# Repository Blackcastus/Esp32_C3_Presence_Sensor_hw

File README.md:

# Esp32_C3_Presence_Sensor_hw
## Thông tin
1. Sử dụng nguồn 220VAC
2. Cảm biến hiện diện HLK-LD2410
3. MCU: ESP32-C3
4. Giao tiếp: USB, UART
5. Extra: DS18820, quang trở
6. Màn hình oled 128
7. Output relay 220VAC
8. Mạch thu RF 315Mhz
9. Màn hình tft ili9341 2.2 inch 18pin

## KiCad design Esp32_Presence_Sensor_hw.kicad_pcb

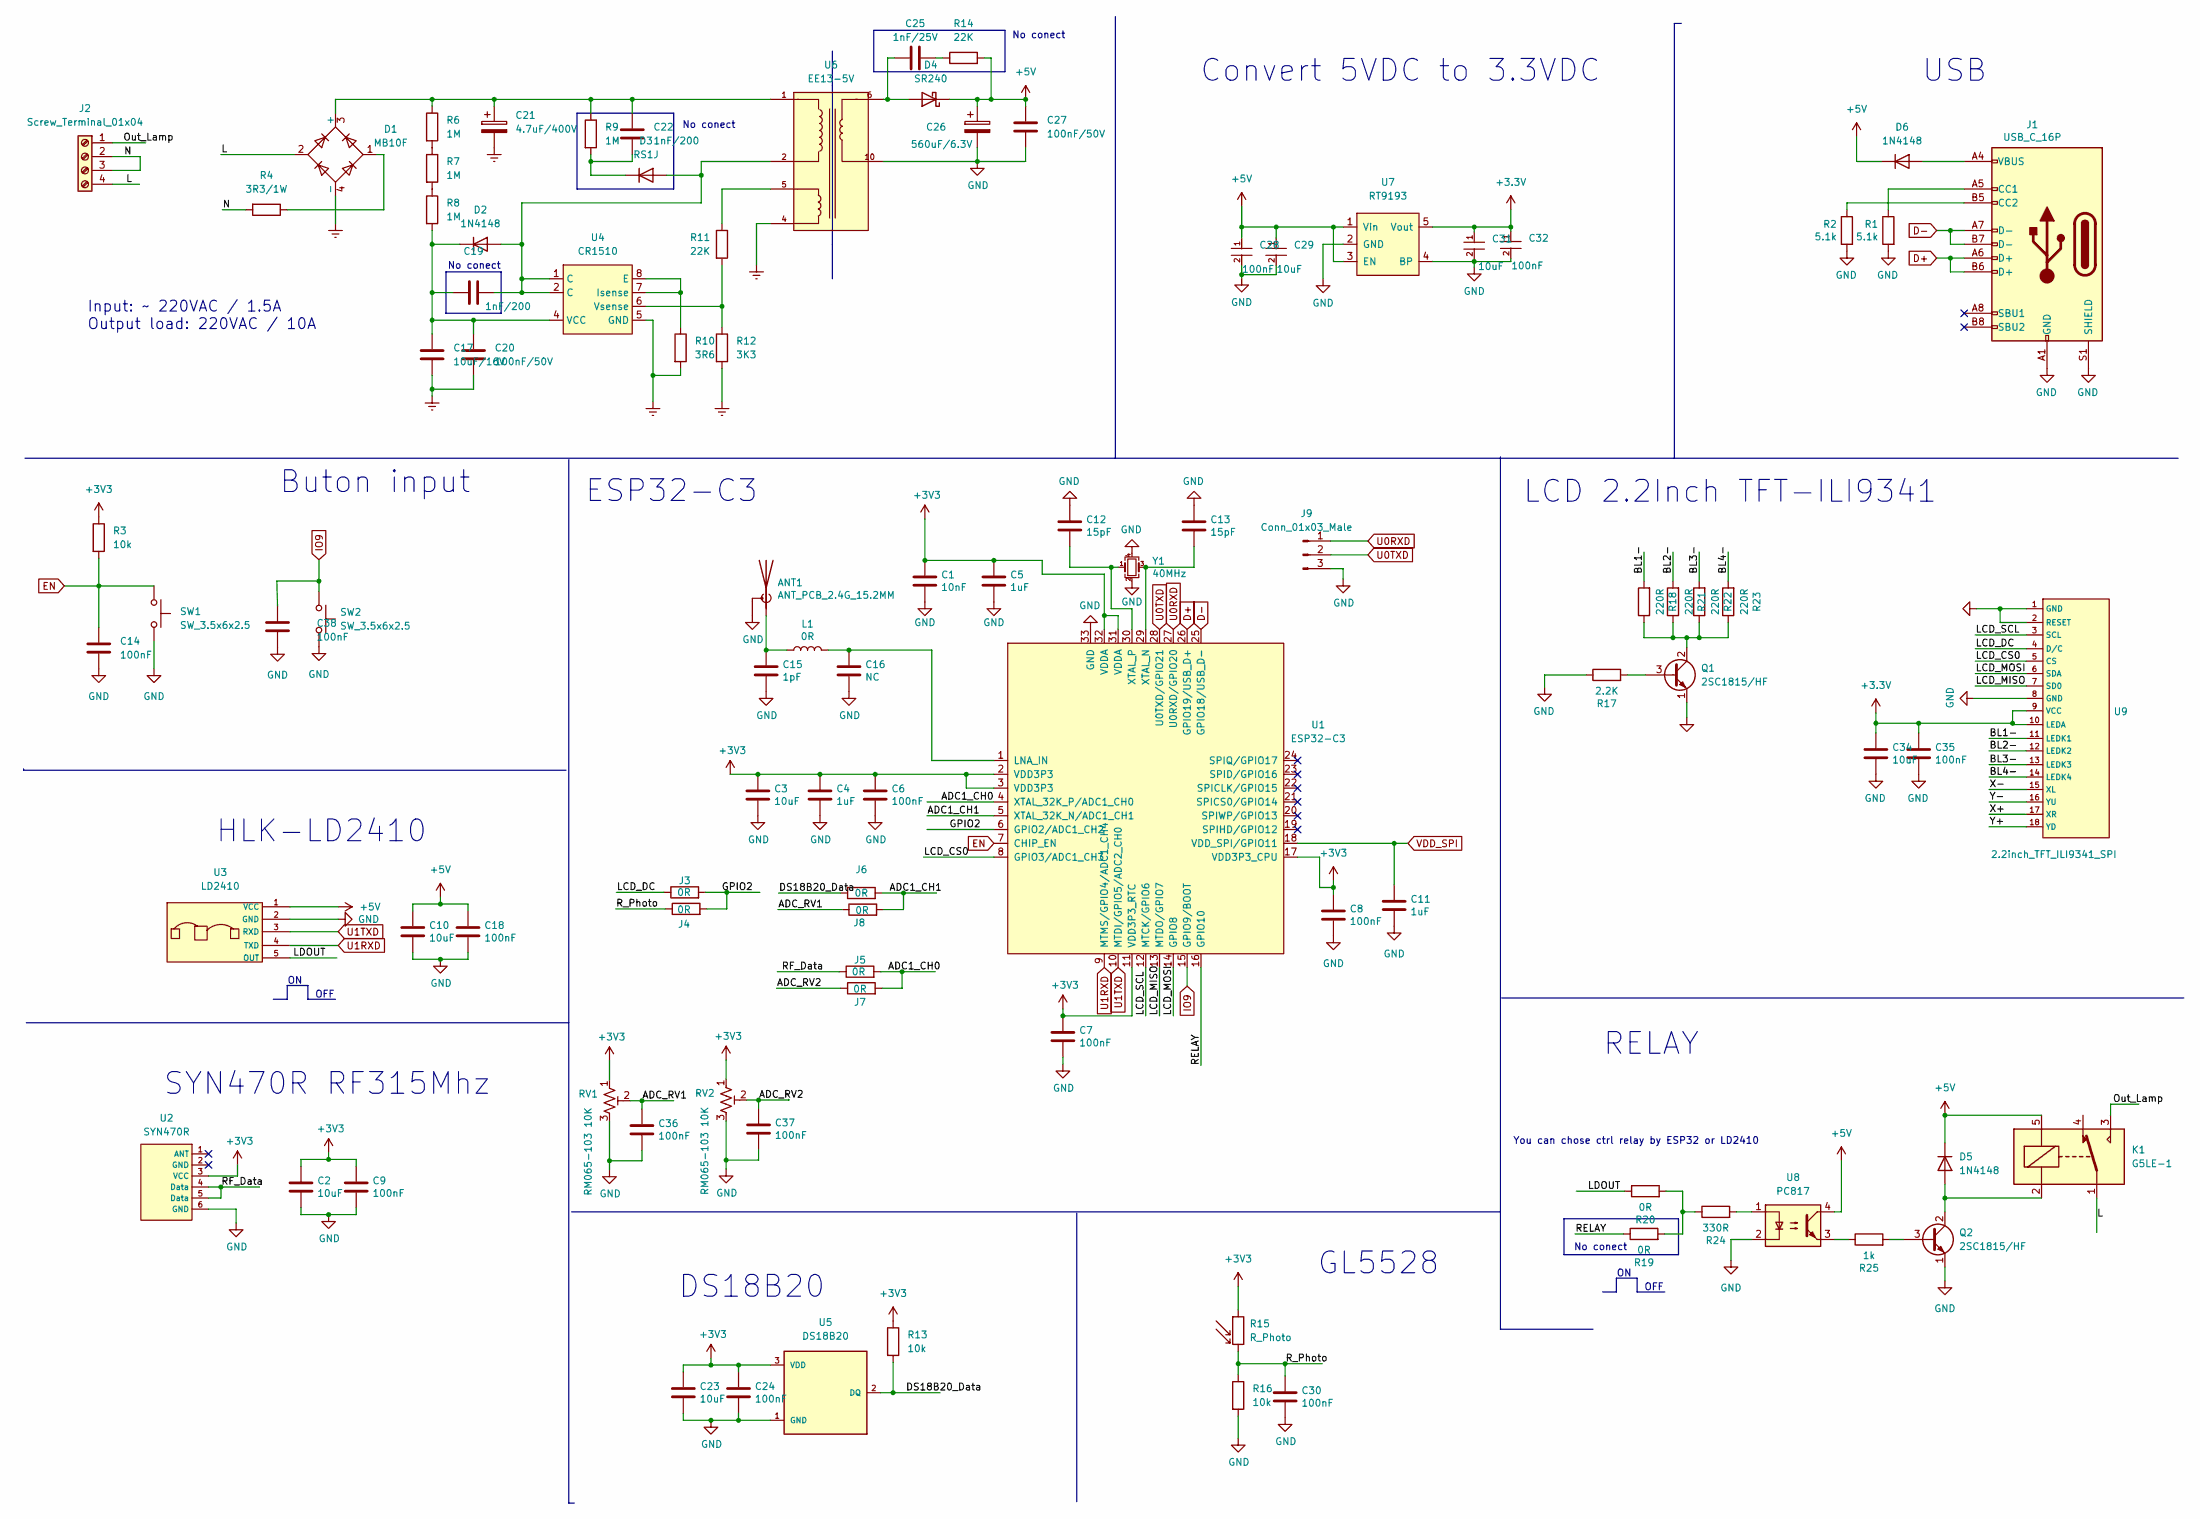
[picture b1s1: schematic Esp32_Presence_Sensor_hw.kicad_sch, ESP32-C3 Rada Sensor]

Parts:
ANT1: ANT_PCB_2.4G_15.2MM; Texas_SWRA117D_2.4GHz_Right
C1: 10nF; C_0805_2012Metric
C2, C3, C10, C23: 10uF; C_0805_2012Metric
C4, C5, C11: 1uF; C_0805_2012Metric
C6, C7, C8, C9, C18, C24, C36, C37, C38: 100nF; C_0805_2012Metric
C12, C13: 15pF; C_0805_2012Metric
C14, C28, C30, C32, C35: 100nF; C_0805_2012Metric_Pad1.18x1.45mm_HandSolder
C15: 1pF; C_0805_2012Metric
C16: NC; C_0805_2012Metric
C17: 10uF/16V; C_0805_2012Metric_Pad1.18x1.45mm_HandSolder
C19, C22: 1nF/200; C_0805_2012Metric_Pad1.18x1.45mm_HandSolder
C20, C27: 100nF/50V; C_0805_2012Metric_Pad1.18x1.45mm_HandSolder
C21: 4.7uF/400V; CP_Radial_D8.0mm_P3.50mm
C25: 1nF/25V; C_0805_2012Metric_Pad1.18x1.45mm_HandSolder
C26: 560uF/6.3V; CP_Radial_D6.3mm_P2.50mm
C29, C31, C34: 10uF; C_0805_2012Metric_Pad1.18x1.45mm_HandSolder
D1: MB10F; TO-269AA
D2, D5, D6: 1N4148; D_SMA
D3: RS1J; D_SMA
D4: SR240; D_SMA
J1: USB_C_16P; USB_C_Receptacle_Palconn_UTC16-G
J2: Screw_Terminal_01x04; TerminalBlock_Phoenix_MKDS-1,5-4-5.08_1x04_P5.08mm_Horizont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
J3, J4, J5, J6, J7, J8: 0R; R_0805_2012Metric
J9: Conn_01x03_Male; PinSocket_1x03_P2.54mm_Vertical
K1: G5LE-1; Relay_SPDT_SANYOU_SRD_Series_Form_C
L1: 0R; L_0805_2012Metric
Q1, Q2: 2SC1815/HF; SOT-23
R1, R2: 5.1k; R_0805_2012Metric
R3: 10k; R_0805_2012Metric_Pad1.20x1.40mm_HandSolder
R4: 3R3/1W; R_Axial_DIN0617_L17.0mm_D6.0mm_P5.08mm_Vertical
R6, R7, R8: 1M; R_1206_3216Metric_Pad1.30x1.75mm_HandSolder
R9: 1M; R_0805_2012Metric
R10: 3R6; R_0805_2012Metric
R11: 22K; R_0805_2012Metric
R12: 3K3; R_0805_2012Metric
R13, R16: 10k; R_0805_2012Metric
R14: 22K; R_1206_3216Metric_Pad1.30x1.75mm_HandSolder
R15: R_Photo; R_photo
R17: 2.2K; R_0805_2012Metric
R18, R21, R22, R23: 220R; R_0805_2012Metric_Pad1.20x1.40mm_HandSolder
R19, R20: 0R; R_0805_2012Metric_Pad1.20x1.40mm_HandSolder
R24: 330R; R_0805_2012Metric_Pad1.20x1.40mm_HandSolder
R25: 1k; R_0805_2012Metric_Pad1.20x1.40mm_HandSolder
RV1, RV2: RM065-103 10K; Potentiometer_Runtron_RM-065_Vertical
SW1, SW2: SW_3.5x6x2.5; SW_DIP_SPSTx01_Slide_6.7x4.1mm_W8.61mm_P2.54mm_LowProfile
U1: ESP32-C3; QFN-32-1EP_5x5mm_P0.5mm_EP3.45x3.45mm
U2: SYN470R; SYN470R_RF315Mhz
U3: LD2410
U4: CR1510; PowerIntegrations_SO-8C
U5: DS18B20; TO-92-TO92127P495H2044-3; PARTREV 5
U6: EE13-5V; EE13_6_6; PARTREV 11/19
U7: RT9193; SOT-23-5_HandSoldering
U8: PC817; SMDIP-4_W9.53mm
U9: 2.2inch_TFT_ILI9341_SPI; TFT_ILI9341_2.2INCH
Y1: 40MHz; Crystal_SMD_TXC_7M-4Pin_3.2x2.5mm

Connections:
+3.3V: C31.1, C32.1, C34.1, C35.1, U7.5 (Vout), U9.9 (VCC), U9.10 (LEDA)
+3V3: C1.1, C2.1, C3.1, C4.1, C5.1, C6.1, C7.1, C8.1, C9.1, C23.1, C24.1, R3.1, R13.1, R15.1, RV1.1, RV2.1, U1.2 (VDD3P3), U1.3 (VDD3P3), U1.11 (VDD3P3_RTC), U1.17 (VDD3P3_CPU), U1.31 (VDDA), U1.32 (VDDA), U2.3 (VCC), U5.3 (VDD)
+5V: C10.1, C18.1, C26.1, C27.1, C28.1, C29.1, D4.1 (K), D5.1 (K), D6.1 (K), K1.5, R14.2, U3.1 (VCC), U7.1 (Vin), U7.3 (EN), U8.4
/ADC1_CH0: J5.2, J7.2, U1.4 (XTAL_32K_P/ADC1_CH0)
/ADC1_CH1: J6.2, J8.2, U1.5 (XTAL_32K_N/ADC1_CH1)
/ADC_RV1: C36.1, J8.1, RV1.2
/ADC_RV2: C37.1, J7.1, RV2.2
/BL1-: R18.2, U9.11 (LEDK1)
/BL2-: R21.2, U9.12 (LEDK2)
/BL3-: R22.2, U9.13 (LEDK3)
/BL4-: R23.2, U9.14 (LEDK4)
/DS18B20_Data: J6.1, R13.2, U5.2 (DQ)
/GPIO2: J3.2, J4.2, U1.6 (GPIO2/ADC1_CH2)
/L: D1.2, J2.4, K1.1
/LCD_CS0: U1.8 (GPIO3/ADC1_CH3), U9.5 (CS)
/LCD_DC: J3.1, U9.4 (D/C)
/LCD_MISO: U1.13 (MTDO/GPIO7), U9.7 (SD0)
/LCD_MOSI: U1.14 (GPIO8), U9.6 (SDA)
/LCD_SCL: U1.12 (MTCK/GPIO6), U9.3 (SCL)
/LDOUT: R20.1, U3.5 (OUT)
/N: J2.2, J2.3, R4.2
/Out_Lamp: J2.1, K1.3
/RELAY: R19.1, U1.16 (GPIO10)
/RF_Data: J5.1, U2.4 (Data), U2.5 (Data)
/R_Photo: C30.1, J4.1, R15.2, R16.1
/X+: U9.17 (XR)
/X-: U9.15 (XL)
/Y+: U9.18 (YD)
/Y-: U9.16 (YU)
D+: J1.A6 (D+), J1.B6 (D+), U1.26 (GPIO19/USB_D+)
D-: J1.A7 (D-), J1.B7 (D-), U1.25 (GPIO18/USB_D-)
EN: C14.1, R3.2, SW1.1, U1.7 (CHIP_EN)
Earth: C17.2, C20.2, C21.2, D1.4 (-), R10.2, R12.2, U4.5 (GND), U6.4
GND: ANT1.2 (Shield), C1.2, C2.2, C3.2, C4.2, C5.2, C6.2, C7.2, C8.2, C9.2, C10.2, C11.2, C12.1, C13.1, C14.2, C15.2, C16.2, C18.2, C23.2, C24.2, C26.2, C27.2, C28.2, C29.2, C30.2, C31.2, C32.2, C34.2, C35.2, C36.2, C37.2, C38.2, J1.A1 (GND), J1.A12 (GND), J1.B1 (GND), J1.B12 (GND), J1.S1 (SHIELD), J9.3, Q1.1 (E), Q2.1 (E), R1.2, R2.2, R16.2, R17.1, RV1.3, RV2.3, SW1.2, SW2.2, U1.33 (GND), U2.6 (GND), U3.2 (GND), U5.1 (GND), U6.10, U7.2 (GND), U7.4 (BP), U8.2, U9.1 (GND), U9.2 (RESET), U9.8 (GND), Y1.2, Y1.4
IO9: C38.1, SW2.1, U1.15 (GPIO9/BOOT)
unnamed: ANT1.1 (A), C15.1, L1.1
unnamed: C25.2, R14.1
unnamed: C21.1, C22.2, D1.3 (+), R6.1, R9.1, U6.1
unnamed: D1.1, R4.1
unnamed: C19.2, D2.2 (A), D3.2 (A), U4.1 (C), U4.2 (C), U6.2
unnamed: C17.1, C19.1, C20.1, D2.1 (K), R8.2, U4.4 (VCC)
unnamed: C22.1, D3.1 (K), R9.2
unnamed: C25.1, D4.2 (A), U6.6
unnamed: D5.2 (A), K1.2, Q2.2 (C)
unnamed: D6.2 (A), J1.A4 (VBUS), J1.A9 (VBUS), J1.B4 (VBUS), J1.B9 (VBUS)
unnamed: J1.A5 (CC1), R1.1
unnamed: J1.B5 (CC2), R2.1
unnamed: Q1.3 (B), R17.2
unnamed: Q1.2 (C), R18.1, R21.1, R22.1, R23.1
unnamed: Q2.3 (B), R25.2
unnamed: R6.2, R7.1
unnamed: R7.2, R8.1
unnamed: R11.1, U6.5
unnamed: R19.2, R20.2, R24.1
unnamed: R24.2, U8.1
unnamed: R25.1, U8.3
unnamed: C16.1, L1.2, U1.1 (LNA_IN)
unnamed: C13.2, U1.29 (XTAL_N), Y1.3
unnamed: C12.2, U1.30 (XTAL_P), Y1.1
unnamed: R10.1, U4.7 (Isense), U4.8 (E)
unnamed: R11.2, R12.1, U4.6 (Vsense)
U0RXD: J9.1, U1.27 (U0RXD/GPIO20)
U0TXD: J9.2, U1.28 (U0TXD/GPIO21)
U1RXD: U1.9 (MTMS/GPIO4/ADC1_CH4), U3.4 (TXD)
U1TXD: U1.10 (MTDI/GPIO5/ADC2_CH0), U3.3 (RXD)
VDD_SPI: C11.1, U1.18 (VDD_SPI/GPIO11)

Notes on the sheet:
No conect
GL5528
LCD 2.2Inch TFT-ILI9341
Buton input
You can chose ctrl relay by ESP32 or LD2410
SYN470R RF315Mhz
Input: ~ 220VAC / 1.5A Output load: 220VAC / 10A
ESP32-C3
RELAY
USB
OFF
DS18B20
HLK-LD2410
Convert 5VDC to 3.3VDC

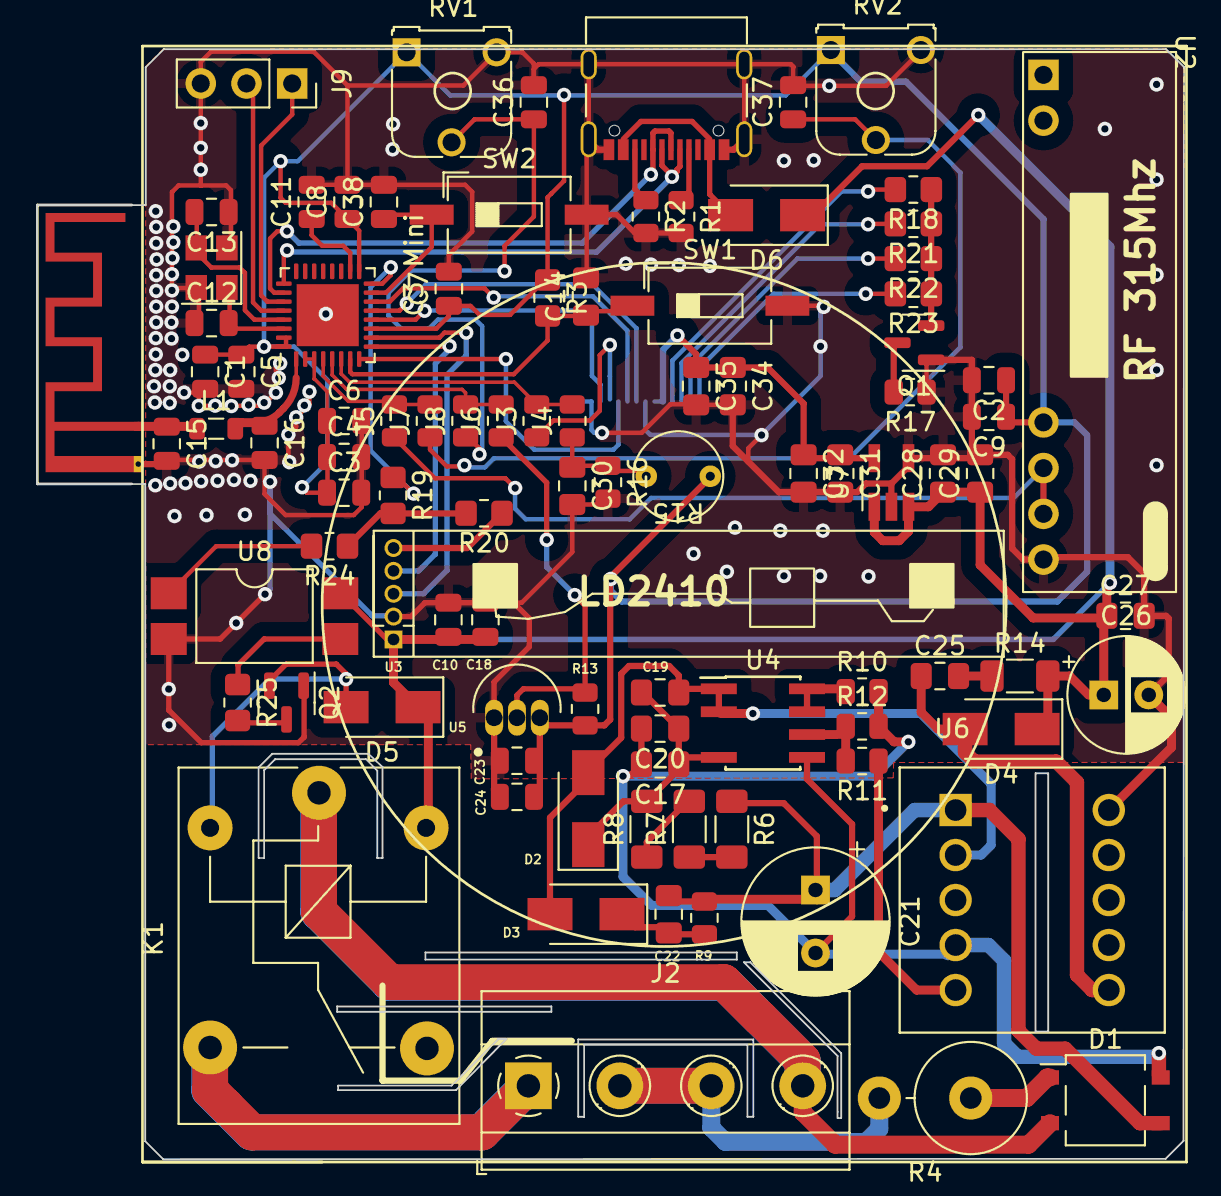
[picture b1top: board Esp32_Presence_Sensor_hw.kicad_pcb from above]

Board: 2 copper layers, 63.7 x 61.7 mm, 95 parts (1 on the bottom side), 62 nets.

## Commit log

2023-03-30 Block(usb, power 5v, esp32-c3)
2023-03-31 Block (220VAC, DS18B20, Resitor photo, relay, oled, RF 315Mhz)
2023-04-03 Xep block nguan 220VAC
2023-04-11 Size box
2023-04-11 Size 2 box
2023-04-15 them bien tro
2023-04-15 sap xep linh kien qua pcb
2023-04-17 Ve xong PCB
2023-05-03 modified block LCD (sch & pcb)
